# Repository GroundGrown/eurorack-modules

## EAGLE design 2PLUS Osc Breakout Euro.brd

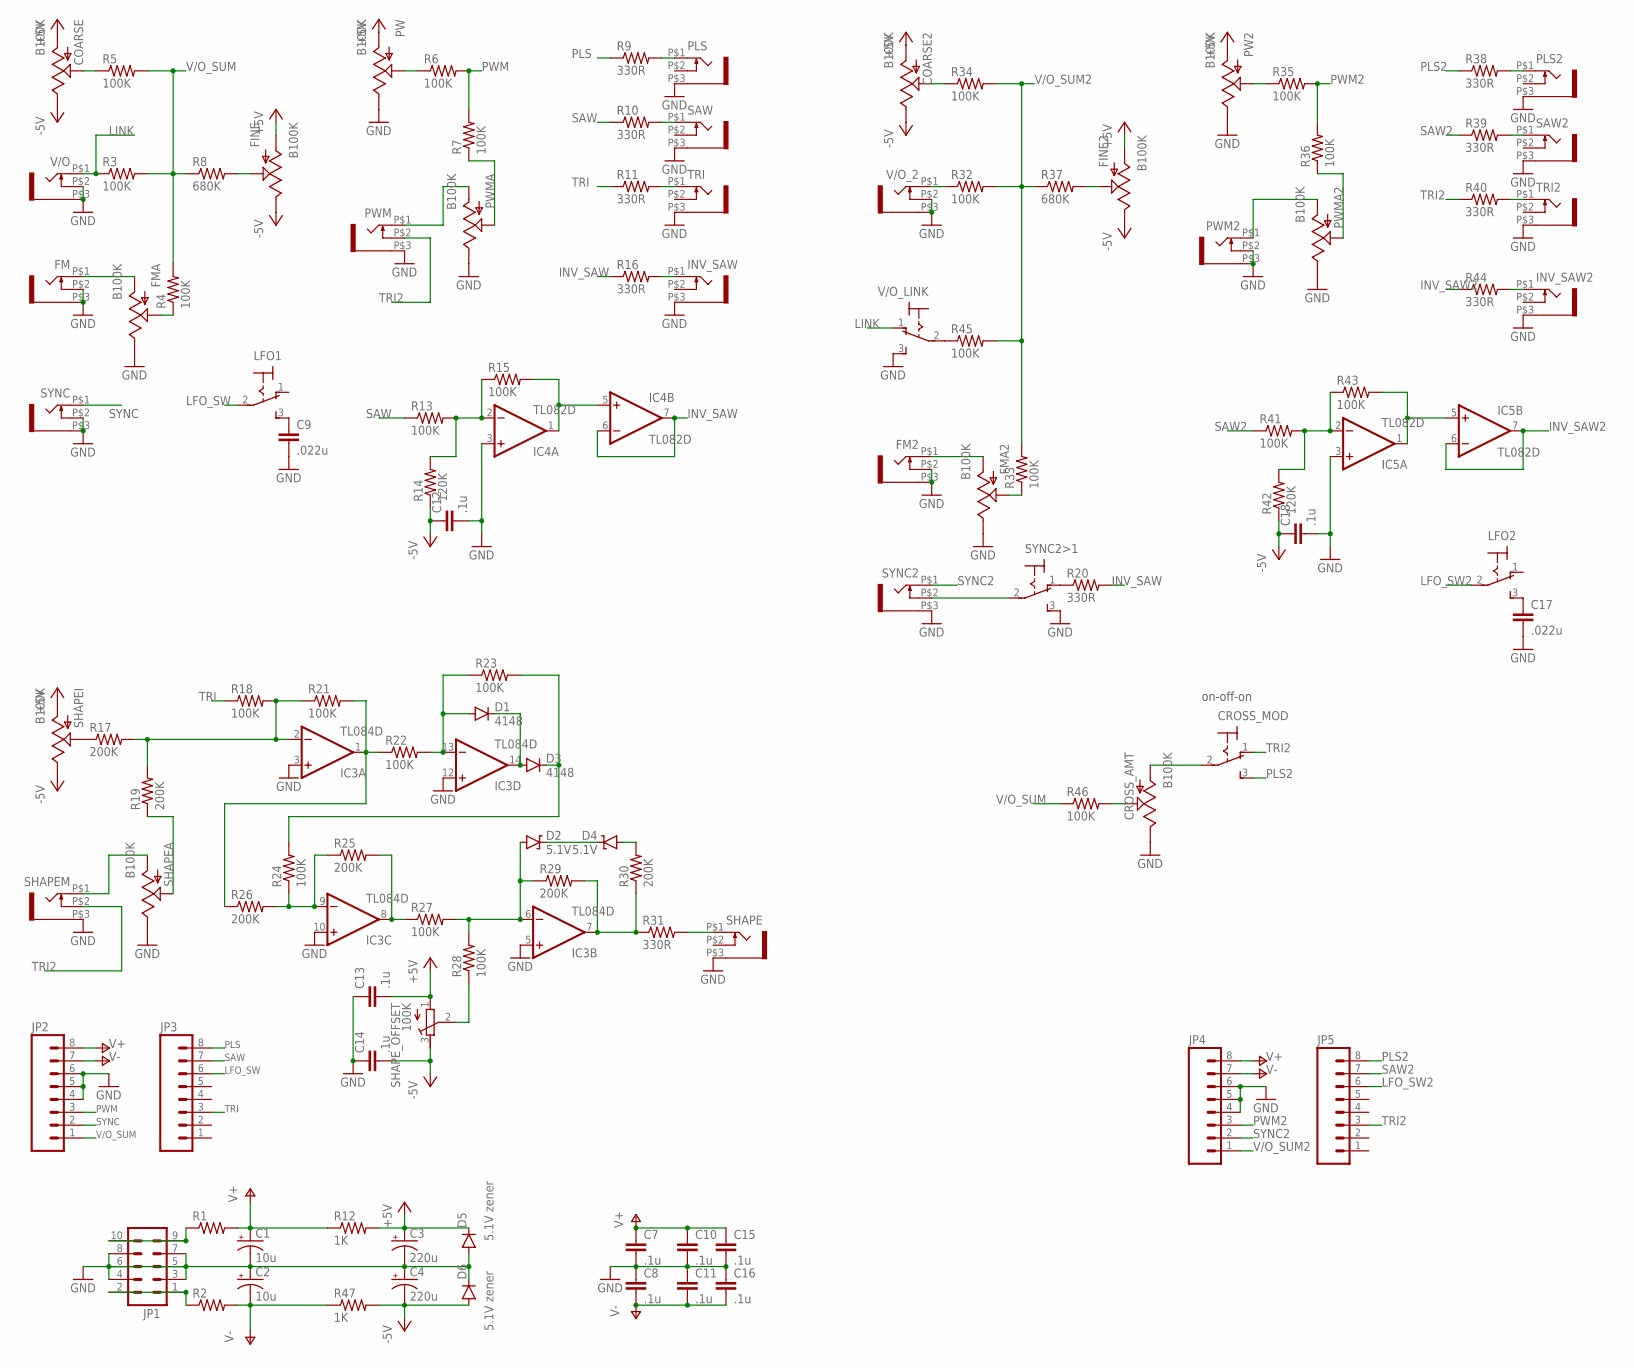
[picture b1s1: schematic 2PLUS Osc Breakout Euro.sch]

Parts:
C1, C2: 10u; PANASONIC_C
C3, C4: 220u; E2,5-5
C7, C8, C10, C11, C12, C13, C14, C15, C16, C18: .1u; 0805
C9, C17: .022u; 0805
COARSE, COARSE2: B100K; ALPS_POT
CROSS_AMT: B100K; ALPS_POT
CROSS_MOD: M9040P
D1, D3: 4148; SOD-123
D2, D4: 5.1V; SOD-123
D5, D6: 5.1V zener; SOD-123
FINE, FINE2: B100K; ALPS_POT
FM, FM2: WQP-PJ301M-12_JACK
FMA, FMA2: B100K; ALPS_POT
IC3: TL084D; SO14
IC4, IC5: TL082D; SO08
INV_SAW, INV_SAW2: WQP-PJ301M-12_JACK
JP1: M05X2PTH; AVR_ICSP
JP2, JP3, JP4, JP5: M08; 1X08_ROUND
LFO1, LFO2: M9040P
PLS, PLS2: WQP-PJ301M-12_JACK
PW, PW2: B100K; ALPS_POT
PWM, PWM2: WQP-PJ301M-12_JACK
PWMA, PWMA2: B100K; ALPS_POT
R1, R2: RESISTOR0805-RES; 0805
R3, R4, R5, R6, R7, R13, R15, R18, R21, R22, R23, R24, R27, R28, R32, R33, R34, R35, R36, R41, R43, R45, R46: 100K; 0805
R8, R37: 680K; 0805
R9, R10, R11, R16, R20, R31, R38, R39, R40, R44: 330R; 0805
R12, R47: 1K; 0805
R14, R42: 120K; 0805
R17, R19, R25, R26, R29, R30: 200K; 0805
SAW, SAW2: WQP-PJ301M-12_JACK
SHAPE: WQP-PJ301M-12_JACK
SHAPEA: B100K; ALPS_POT
SHAPEI: B100K; ALPS_POT
SHAPEM: WQP-PJ301M-12_JACK
SHAPE_OFFSET: 100K; RTRIM3296Y
SYNC, SYNC2: WQP-PJ301M-12_JACK
SYNC2>1: M9040P
TRI, TRI2: WQP-PJ301M-12_JACK
V/O: WQP-PJ301M-12_JACK
V/O_2: WQP-PJ301M-12_JACK
V/O_LINK: M9040P

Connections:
+5V: C3.+, C13.2, COARSE.P$3 (A), COARSE2.P$3 (A), D5.C, FINE.P$3 (A), FINE2.P$3 (A), PW.P$3 (A), PW2.P$3 (A), R12.2, SHAPEI.P$3 (A), SHAPE_OFFSET.1 (A)
-5V: C4.-, C12.1, C14.2, C18.1, COARSE.P$1 (E), COARSE2.P$1 (E), D6.A, FINE.P$1 (E), FINE2.P$1 (E), R14.1, R42.1, R47.2, SHAPEI.P$1 (E), SHAPE_OFFSET.3 (E)
GND: C1.-, C2.+, C3.-, C4.+, C7.2, C8.1, C9.2, C10.2, C11.1, C12.2, C13.1, C14.1, C15.2, C16.1, C17.2, C18.2, CROSS_AMT.P$1 (E), D5.A, D6.C, FM.P$2 (3), FM.P$3 (1), FM2.P$2 (3), FM2.P$3 (1), FMA.P$1 (E), FMA2.P$1 (E), IC3.3 (+IN), IC3.5 (+IN), IC3.10 (+IN), IC3.12 (+IN), IC4.3 (+IN), IC5.3 (+IN), INV_SAW.P$3 (1), INV_SAW2.P$3 (1), JP1.3, JP1.4, JP1.5, JP1.6, JP1.7, JP1.8, JP2.4, JP2.5, JP2.6, JP4.4, JP4.5, JP4.6, PLS.P$3 (1), PLS2.P$3 (1), PW.P$1 (E), PW2.P$1 (E), PWM.P$3 (1), PWM2.P$2 (3), PWM2.P$3 (1), PWMA.P$1 (E), PWMA2.P$1 (E), SAW.P$3 (1), SAW2.P$3 (1), SHAPE.P$3 (1), SHAPEA.P$1 (E), SHAPEM.P$3 (1), SYNC.P$2 (3), SYNC.P$3 (1), SYNC2.P$3 (1), SYNC2>1.3 (S), TRI.P$3 (1), TRI2.P$3 (1), V/O.P$2 (3), V/O.P$3 (1), V/O_2.P$2 (3), V/O_2.P$3 (1), V/O_LINK.3 (S)
INV_SAW: IC4.6 (-IN), IC4.7 (OUT), R16.1, R20.2
INV_SAW2: IC5.6 (-IN), IC5.7 (OUT), R44.1
LFO_SW: JP3.6, LFO1.2
LFO_SW2: JP5.6, LFO2.2
LINK: R3.1, V/O.P$1 (2), V/O_LINK.1 (O)
unnamed: JP1.9, JP1.10, R1.1
unnamed: JP1.1, JP1.2, R2.1
unnamed: FM.P$1 (2), FMA.P$3 (A)
unnamed: COARSE.P$2 (S), R5.1
unnamed: R45.1, V/O_LINK.2
unnamed: FMA.P$2 (S), R4.1
unnamed: PW.P$2 (S), R6.1
unnamed: PWM.P$1 (2), PWMA.P$3 (A)
unnamed: FINE.P$2 (S), R8.2
unnamed: C9.1, LFO1.3 (S)
unnamed: PWMA.P$2 (S), R7.1
unnamed: PLS.P$1 (2), R9.2
unnamed: R10.2, SAW.P$1 (2)
unnamed: R11.2, TRI.P$1 (2)
unnamed: IC4.2 (-IN), R13.2, R14.2, R15.1
unnamed: IC3.2 (-IN), R17.2, R18.2, R19.2, R21.1
unnamed: IC4.1 (OUT), IC4.5 (+IN), R15.2
unnamed: CROSS_AMT.P$2 (S), R46.2
unnamed: INV_SAW.P$1 (2), R16.2
unnamed: R17.1, SHAPEI.P$2 (S)
unnamed: SHAPEA.P$3 (A), SHAPEM.P$1 (2)
unnamed: R19.1, SHAPEA.P$2 (S)
unnamed: SYNC2.P$2 (3), SYNC2>1.2
unnamed: IC3.1 (OUT), R21.2, R22.1, R26.1
unnamed: D1.C, D3.A, IC3.14 (OUT)
unnamed: D1.A, IC3.13 (-IN), R22.2, R23.1
unnamed: D3.C, R23.2, R24.2
unnamed: IC3.9 (-IN), R24.1, R25.1, R26.2
unnamed: IC3.8 (OUT), R25.2, R27.1
unnamed: D2.A, IC3.6 (-IN), R27.2, R28.2, R29.1
unnamed: R28.1, SHAPE_OFFSET.2 (S)
unnamed: D2.C, D4.C
unnamed: D4.A, R30.2
unnamed: IC3.7 (OUT), R29.2, R30.1, R31.1
unnamed: R31.2, SHAPE.P$1 (2)
unnamed: COARSE2.P$2 (S), R34.1
unnamed: R32.1, V/O_2.P$1 (2)
unnamed: CROSS_AMT.P$3 (A), CROSS_MOD.2
unnamed: FMA2.P$2 (S), R33.1
unnamed: C17.1, LFO2.3 (S)
unnamed: PW2.P$2 (S), R35.1
unnamed: FINE2.P$2 (S), R37.2
unnamed: PLS2.P$1 (2), R38.2
unnamed: R39.2, SAW2.P$1 (2)
unnamed: R40.2, TRI2.P$1 (2)
unnamed: FM2.P$1 (2), FMA2.P$3 (A)
unnamed: PWM2.P$1 (2), PWMA2.P$3 (A)
unnamed: INV_SAW2.P$1 (2), R44.2
unnamed: PWMA2.P$2 (S), R36.1
unnamed: R20.1, SYNC2>1.1 (O)
unnamed: IC5.2 (-IN), R41.2, R42.2, R43.1
unnamed: IC5.1 (OUT), IC5.5 (+IN), R43.2
PLS: JP3.8, R9.1
PLS2: CROSS_MOD.3 (S), JP5.8, R38.1
PWM: JP2.3, R6.2, R7.2
PWM2: JP4.3, R35.2, R36.2
SAW: JP3.7, R10.1, R13.1
SAW2: JP5.7, R39.1, R41.1
SYNC: JP2.2, SYNC.P$1 (2)
SYNC2: JP4.2, SYNC2.P$1 (2)
TRI: JP3.3, R11.1, R18.1
TRI2: CROSS_MOD.1 (O), JP5.3, PWM.P$2 (3), R40.1, SHAPEM.P$2 (3)
V+: C1.+, C7.1, C10.1, C15.1, IC3.4 (V+), IC4.8 (V+), IC5.8 (V+), JP2.8, JP4.8, R1.2, R12.1
V-: C2.-, C8.2, C11.2, C16.2, IC3.11 (V-), IC4.4 (V-), IC5.4 (V-), JP2.7, JP4.7, R2.2, R47.1
V/O_SUM: JP2.1, R3.2, R4.2, R5.2, R8.1, R46.1
V/O_SUM2: JP4.1, R32.2, R33.2, R34.2, R37.1, R45.2

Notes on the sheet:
on-off-on

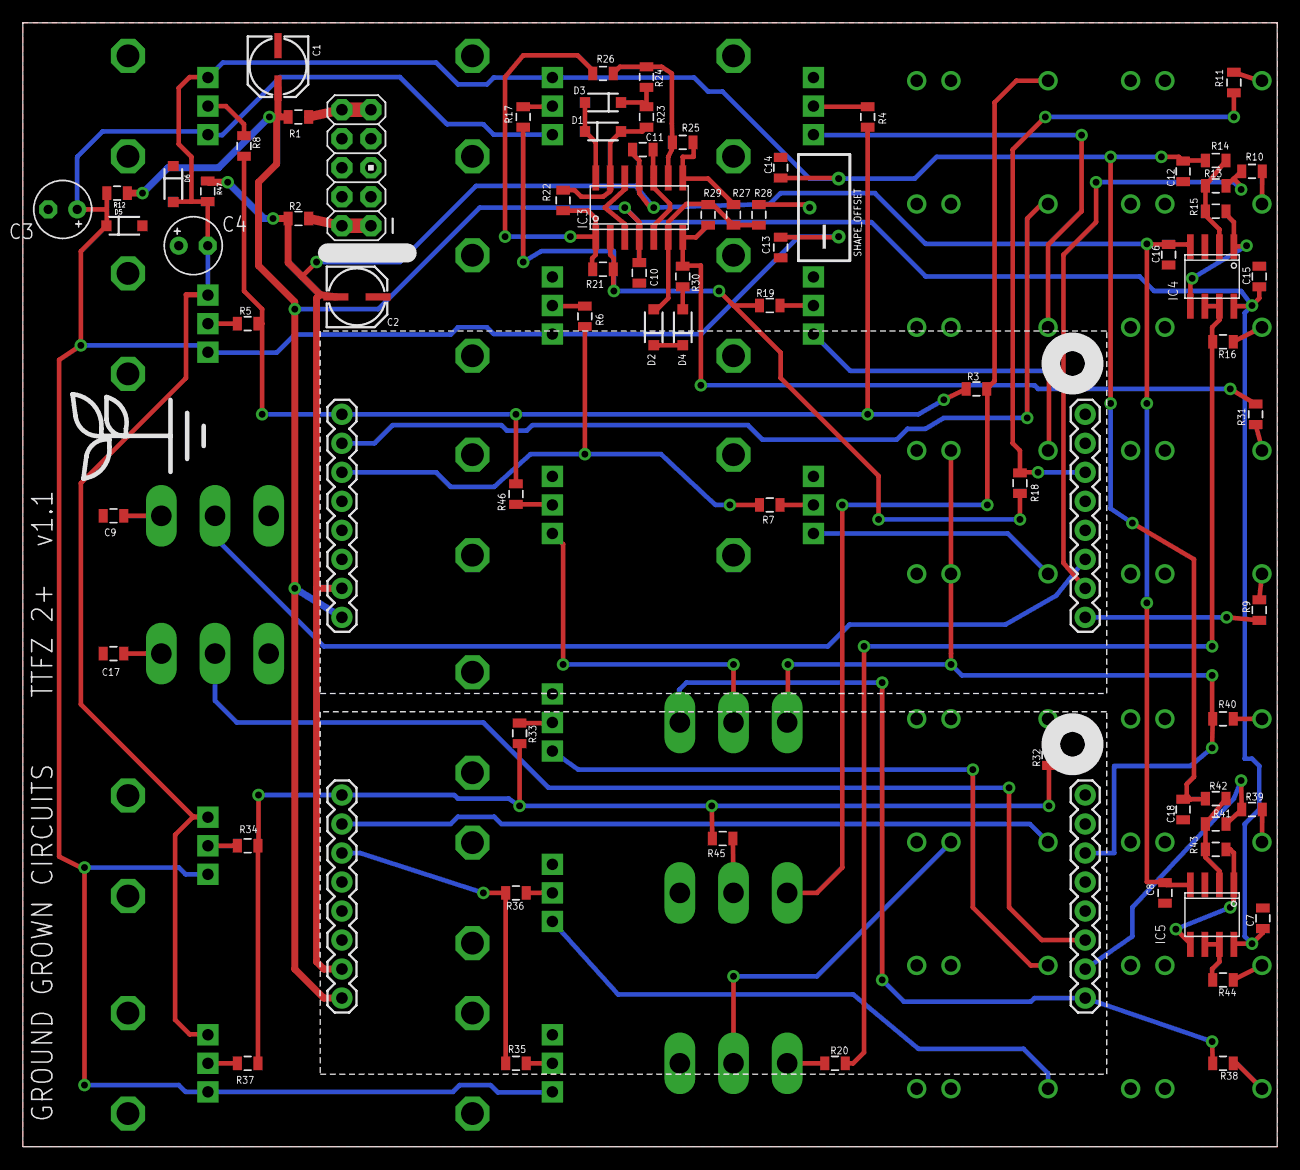
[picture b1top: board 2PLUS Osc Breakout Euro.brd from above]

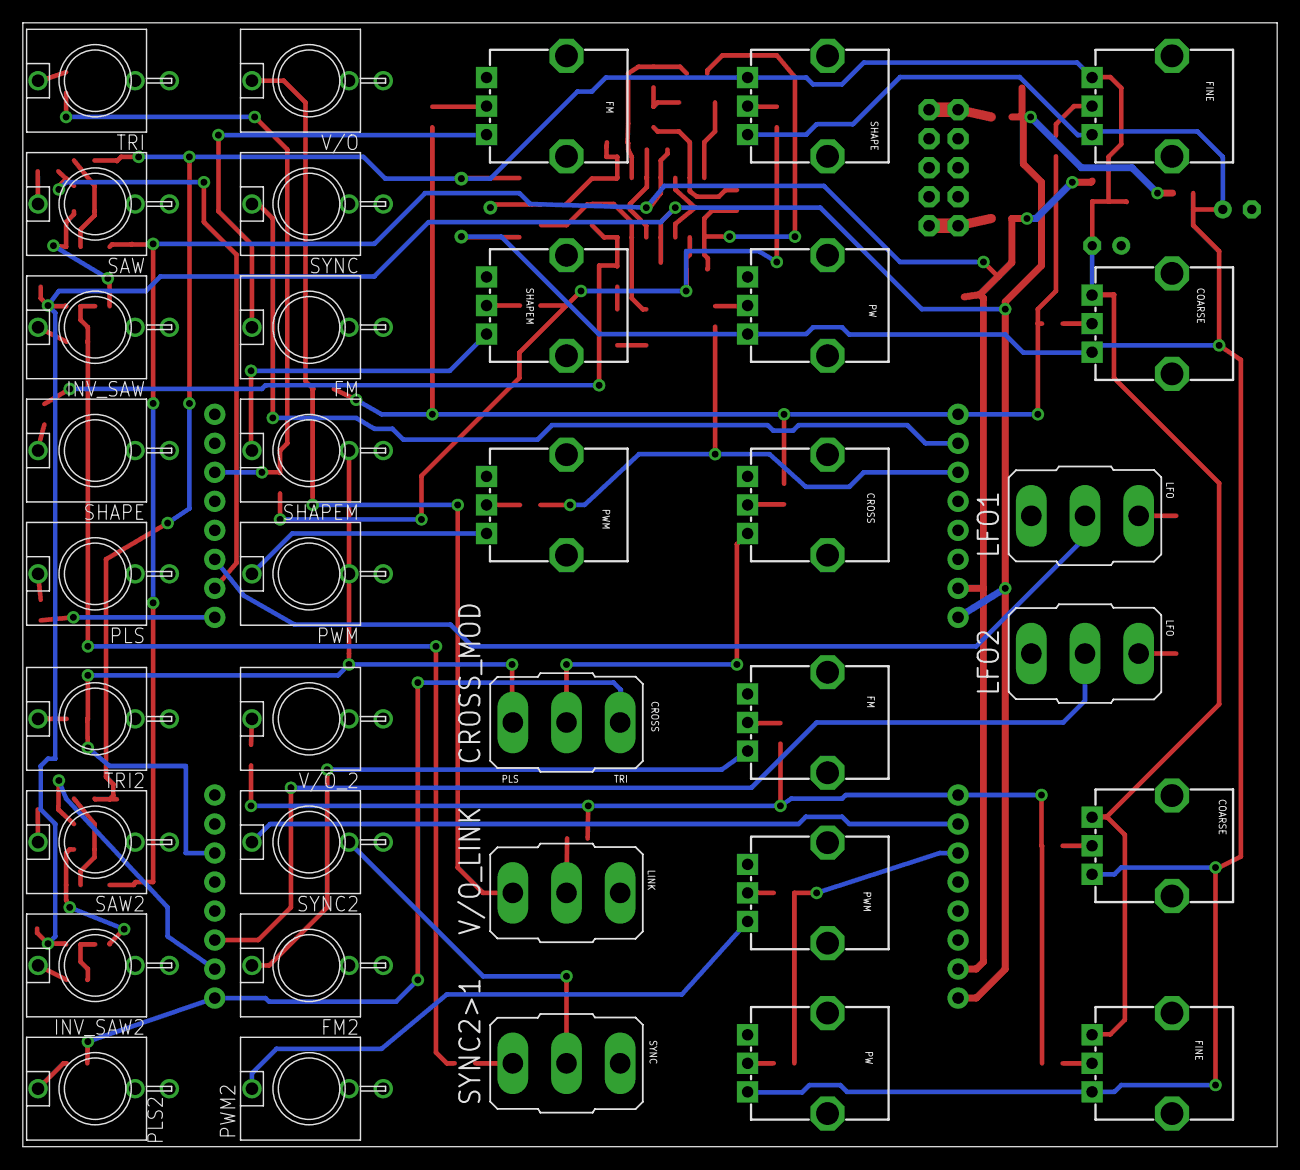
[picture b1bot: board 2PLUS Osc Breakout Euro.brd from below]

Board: 2 copper layers, 109.8 x 98.4 mm, 117 parts (36 on the bottom side), 74 nets.

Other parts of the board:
U$1, U$2: OSC_CORE_OUTLINE
U$3: LOGO_MED

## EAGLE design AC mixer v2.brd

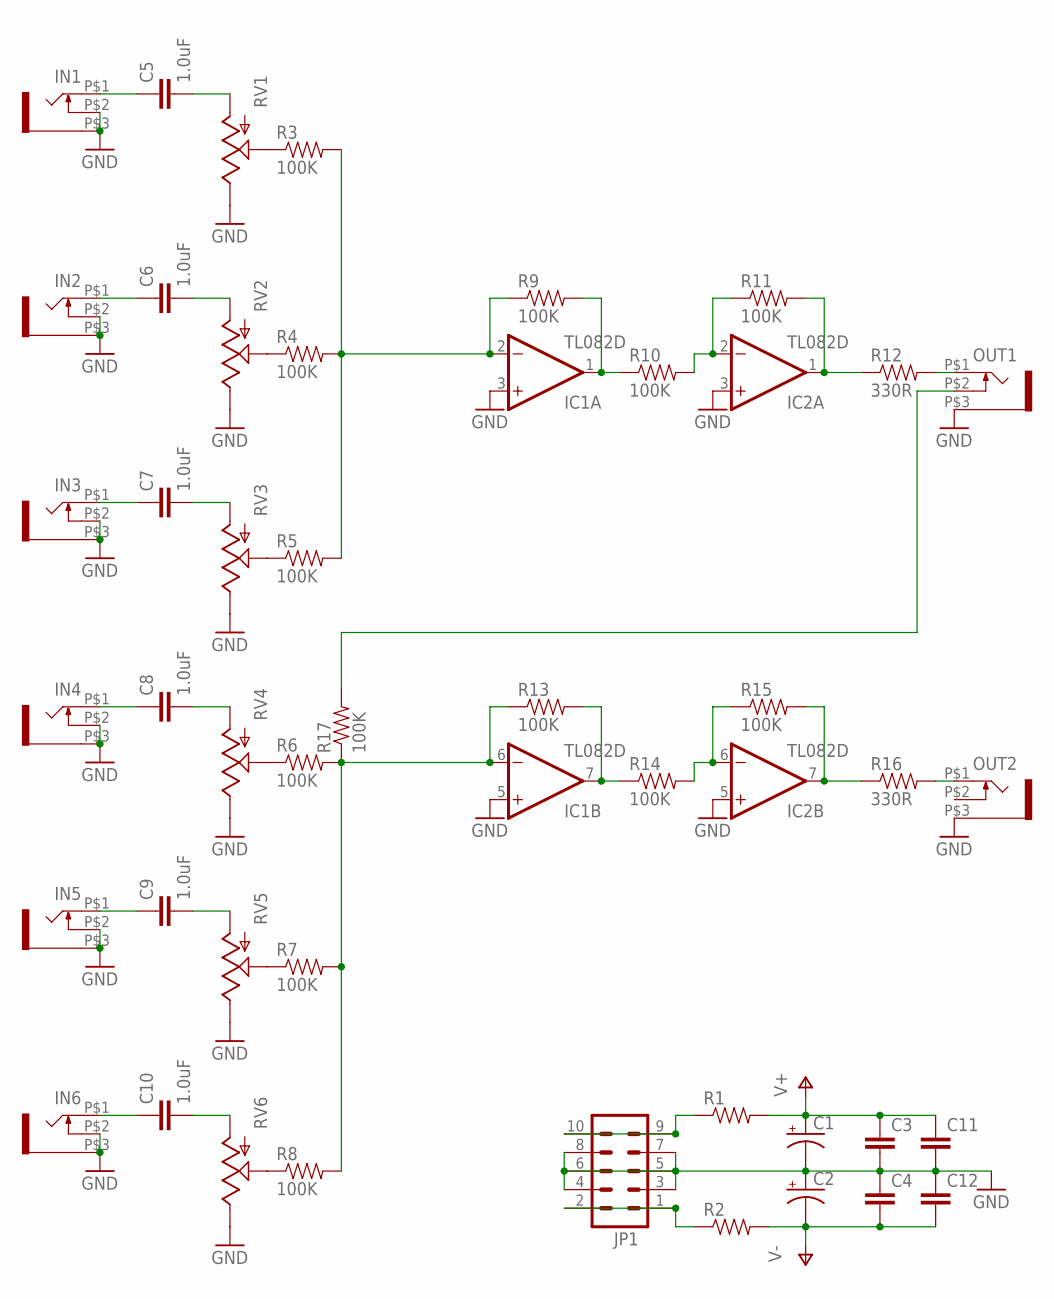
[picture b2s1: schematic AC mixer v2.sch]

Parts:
C1, C2: CAP_POLC; PANASONIC_C
C3, C4, C11, C12: CAP0805; 0805
C5, C6, C7, C8, C9, C10: 1.0uF; 1206
IC1, IC2: TL082D; SO08
IN1, IN2, IN3, IN4, IN5, IN6: WQP-PJ301M-12_JACK
JP1: M05X2PTH; AVR_ICSP
OUT1, OUT2: WQP-PJ301M-12_JACK
R1, R2: RESISTOR0805-RES; 0805
R3, R4, R5, R6, R7, R8, R9, R10, R11, R13, R14, R15, R17: 100K; 0805
R12, R16: 330R; 0805
RV1, RV2, RV3, RV4, RV5, RV6: POT; ALPS_POT

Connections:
GND: C1.-, C2.+, C3.2, C4.1, C11.2, C12.1, IC1.3 (+IN), IC1.5 (+IN), IC2.3 (+IN), IC2.5 (+IN), IN1.P$2 (3), IN1.P$3 (1), IN2.P$2 (3), IN2.P$3 (1), IN3.P$2 (3), IN3.P$3 (1), IN4.P$2 (3), IN4.P$3 (1), IN5.P$2 (3), IN5.P$3 (1), IN6.P$2 (3), IN6.P$3 (1), JP1.3, JP1.4, JP1.5, JP1.6, JP1.7, JP1.8, OUT1.P$3 (1), OUT2.P$3 (1), RV1.P$1 (E), RV2.P$1 (E), RV3.P$1 (E), RV4.P$1 (E), RV5.P$1 (E), RV6.P$1 (E)
unnamed: R3.1, RV1.P$2 (S)
unnamed: C6.1, IN2.P$1 (2)
unnamed: JP1.9, JP1.10, R1.1
unnamed: C6.2, RV2.P$3 (A)
unnamed: R4.1, RV2.P$2 (S)
unnamed: JP1.1, JP1.2, R2.1
unnamed: C7.1, IN3.P$1 (2)
unnamed: C7.2, RV3.P$3 (A)
unnamed: C5.1, IN1.P$1 (2)
unnamed: C5.2, RV1.P$3 (A)
unnamed: R5.1, RV3.P$2 (S)
unnamed: C8.1, IN4.P$1 (2)
unnamed: C8.2, RV4.P$3 (A)
unnamed: R6.1, RV4.P$2 (S)
unnamed: C9.1, IN5.P$1 (2)
unnamed: C9.2, RV5.P$3 (A)
unnamed: R7.1, RV5.P$2 (S)
unnamed: C10.1, IN6.P$1 (2)
unnamed: C10.2, RV6.P$3 (A)
unnamed: R8.1, RV6.P$2 (S)
unnamed: OUT1.P$2 (3), R17.2
unnamed: IC1.1 (OUT), R9.2, R10.1
unnamed: IC2.2 (-IN), R10.2, R11.1
unnamed: IC2.1 (OUT), R11.2, R12.1
unnamed: OUT1.P$1 (2), R12.2
unnamed: IC1.2 (-IN), R3.2, R4.2, R5.2, R9.1
unnamed: IC1.7 (OUT), R13.2, R14.1
unnamed: IC2.6 (-IN), R14.2, R15.1
unnamed: IC2.7 (OUT), R15.2, R16.1
unnamed: OUT2.P$1 (2), R16.2
unnamed: IC1.6 (-IN), R6.2, R7.2, R8.2, R13.1, R17.1
V+: C1.+, C3.1, C11.1, IC1.8 (V+), IC2.8 (V+), R1.2
V-: C2.-, C4.2, C12.2, IC1.4 (V-), IC2.4 (V-), R2.2

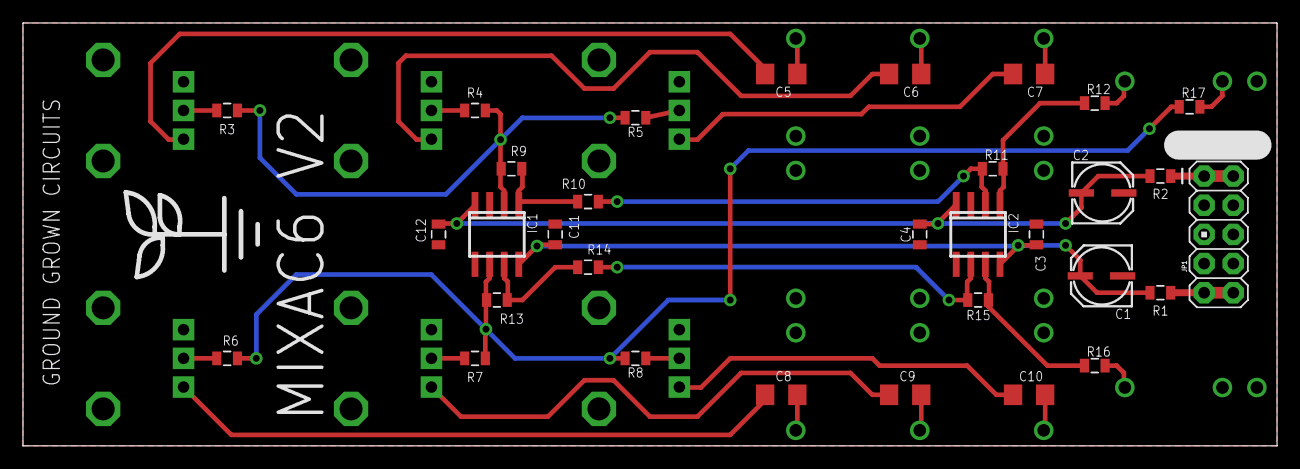
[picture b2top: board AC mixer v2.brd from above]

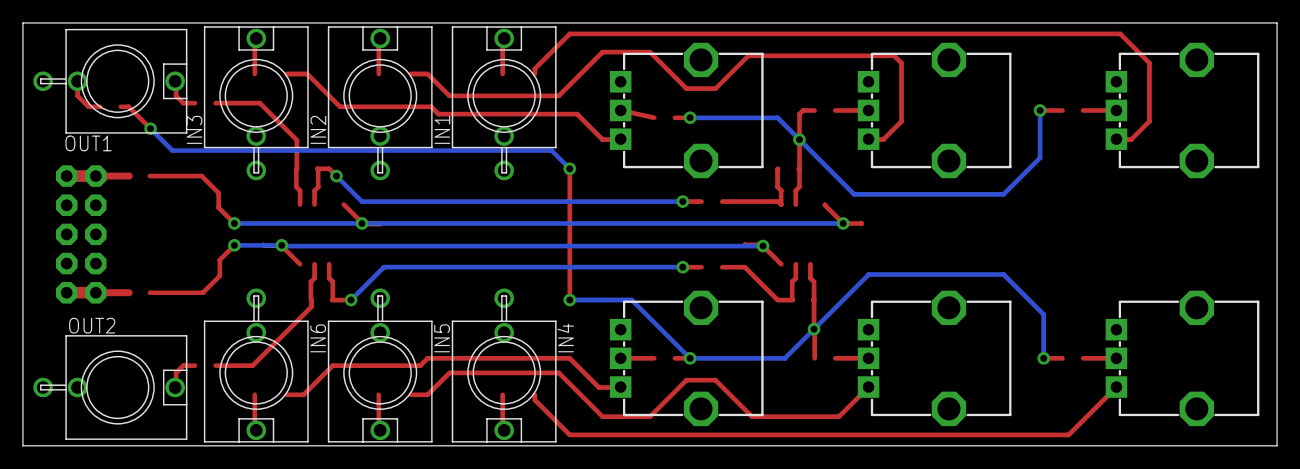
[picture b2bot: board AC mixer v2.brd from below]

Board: 2 copper layers, 109.2 x 36.8 mm, 47 parts (14 on the bottom side), 34 nets.

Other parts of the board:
U$1: LOGO_MED

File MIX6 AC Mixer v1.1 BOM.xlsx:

2 | FERRITE BEAD | R1, R2
1 | 330 ohm | R12
9 | 100K | R3, R4, R5, R6, R7, R8, R9, R10, R11
2 | .1u | C3, C4
6 | 1u Film | C5, C6, C7, C8, C9, C10
2 | 10u | C1, C2
1 | TL082 | IC1
1 | 2x5 pos male .1" Header | JP1
7 | WQP-PJ301M-12_JACK | IN1, IN2, IN3, IN4, IN5, IN6, OUT
6 | B50K | RV1, RV2, RV3, RV4, RV5, RV6

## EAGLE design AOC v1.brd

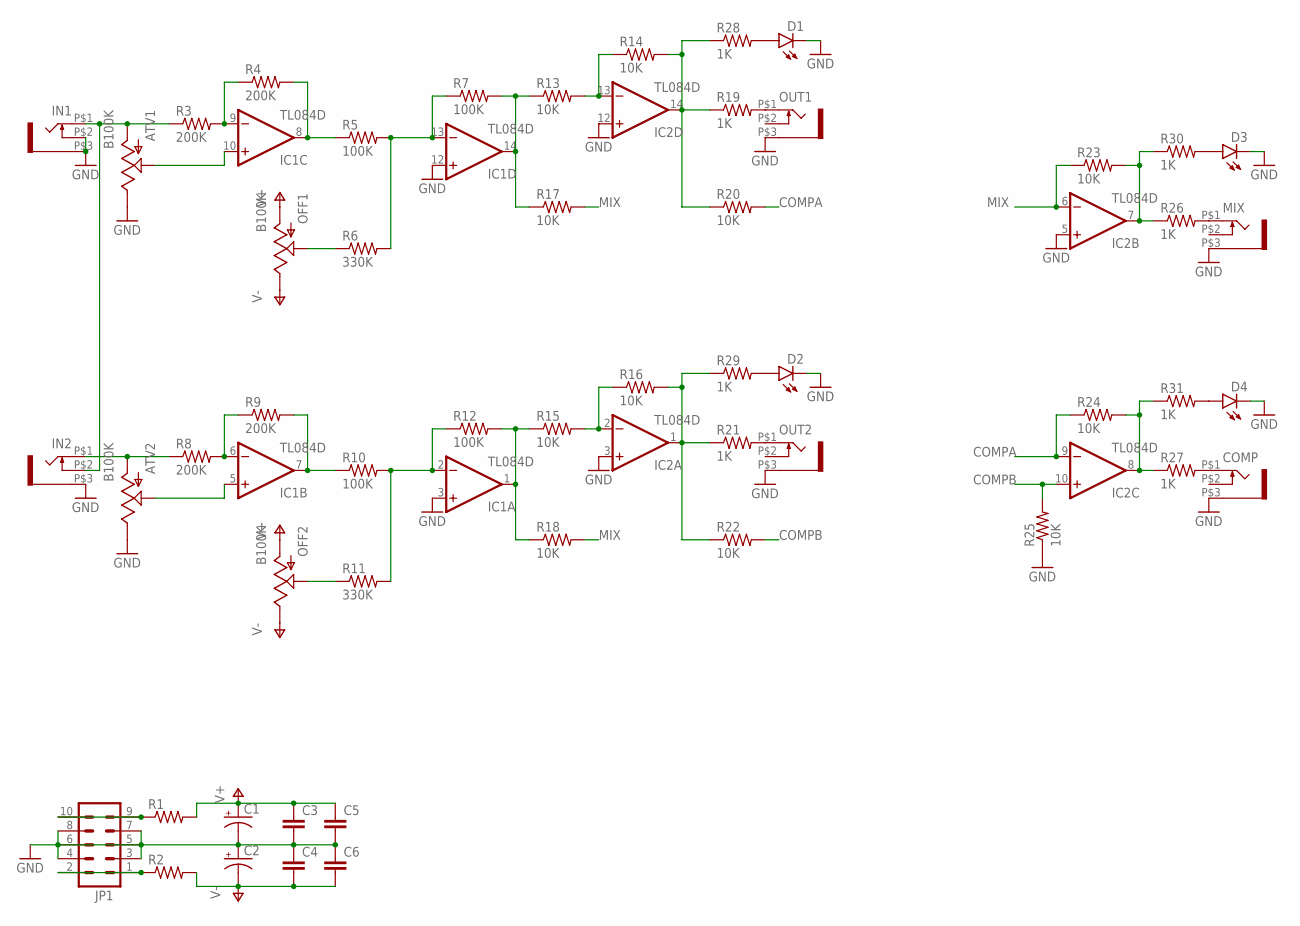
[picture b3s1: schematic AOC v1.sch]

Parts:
ATV1, ATV2: B100K; ALPS_POT
C1, C2: CAP_POLPTH2; CPOL-RADIAL-10UF-25V
C3, C4, C5, C6: CAP0805; 0805
COMP: WQP-PJ301M-12_JACK
D1, D2, D3, D4: LED3MM
IC1, IC2: TL084D; SO14
IN1, IN2: WQP-PJ301M-12_JACK
JP1: M05X2PTH; AVR_ICSP
MIX: WQP-PJ301M-12_JACK
OFF1, OFF2: B100K; ALPS_POT
OUT1, OUT2: WQP-PJ301M-12_JACK
R1, R2: RESISTOR0805-RES; 0805@1
R3, R4, R8, R9: 200K; 0805@1
R5, R7, R10, R12: 100K; 0805@1
R6, R11: 330K; 0805@1
R13, R14, R15, R16, R17, R18, R20, R22, R23, R24, R25: 10K; 0805@1
R19, R21, R26, R27, R28, R29, R30, R31: 1K; 0805@1

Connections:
COMPA: IC2.9 (-IN), R20.2, R24.1
COMPB: IC2.10 (+IN), R22.2, R25.2
GND: ATV1.P$1 (E), ATV2.P$1 (E), C1.2 (-), C2.1 (+), C3.2, C4.1, C5.2, C6.1, COMP.P$3 (1), D1.K (C), D2.K (C), D3.K (C), D4.K (C), IC1.3 (+IN), IC1.12 (+IN), IC2.3 (+IN), IC2.5 (+IN), IC2.12 (+IN), IN1.P$2 (3), IN1.P$3 (1), IN2.P$3 (1), JP1.3, JP1.4, JP1.5, JP1.6, JP1.7, JP1.8, MIX.P$3 (1), OUT1.P$3 (1), OUT2.P$3 (1), R25.1
MIX: IC2.6 (-IN), R17.2, R18.2, R23.1
unnamed: JP1.9, JP1.10, R1.1
unnamed: JP1.1, JP1.2, R2.1
unnamed: IC1.9 (-IN), R3.2, R4.1
unnamed: ATV1.P$3 (A), IN1.P$1 (2), IN2.P$2 (3), R3.1
unnamed: IC1.8 (OUT), R4.2, R5.1
unnamed: ATV1.P$2 (S), IC1.10 (+IN)
unnamed: OFF1.P$2 (S), R6.1
unnamed: IC1.13 (-IN), R5.2, R6.2, R7.1
unnamed: IC1.14 (OUT), R7.2, R13.1, R17.1
unnamed: IC1.6 (-IN), R8.2, R9.1
unnamed: ATV2.P$3 (A), IN2.P$1 (2), R8.1
unnamed: IC1.7 (OUT), R9.2, R10.1
unnamed: ATV2.P$2 (S), IC1.5 (+IN)
unnamed: OFF2.P$2 (S), R11.1
unnamed: IC1.2 (-IN), R10.2, R11.2, R12.1
unnamed: IC1.1 (OUT), R12.2, R15.1, R18.1
unnamed: IC2.13 (-IN), R13.2, R14.1
unnamed: IC2.14 (OUT), R14.2, R19.1, R20.1, R28.1
unnamed: IC2.2 (-IN), R15.2, R16.1
unnamed: IC2.1 (OUT), R16.2, R21.1, R22.1, R29.1
unnamed: MIX.P$1 (2), R26.2
unnamed: IC2.7 (OUT), R23.2, R26.1, R30.1
unnamed: OUT1.P$1 (2), R19.2
unnamed: OUT2.P$1 (2), R21.2
unnamed: IC2.8 (OUT), R24.2, R27.1, R31.1
unnamed: COMP.P$1 (2), R27.2
unnamed: D1.A, R28.2
unnamed: D2.A, R29.2
unnamed: D3.A, R30.2
unnamed: D4.A, R31.2
V+: C1.1 (+), C3.1, C5.1, IC1.4 (V+), IC2.4 (V+), OFF1.P$3 (A), OFF2.P$3 (A), R1.2
V-: C2.2 (-), C4.2, C6.2, IC1.11 (V-), IC2.11 (V-), OFF1.P$1 (E), OFF2.P$1 (E), R2.2

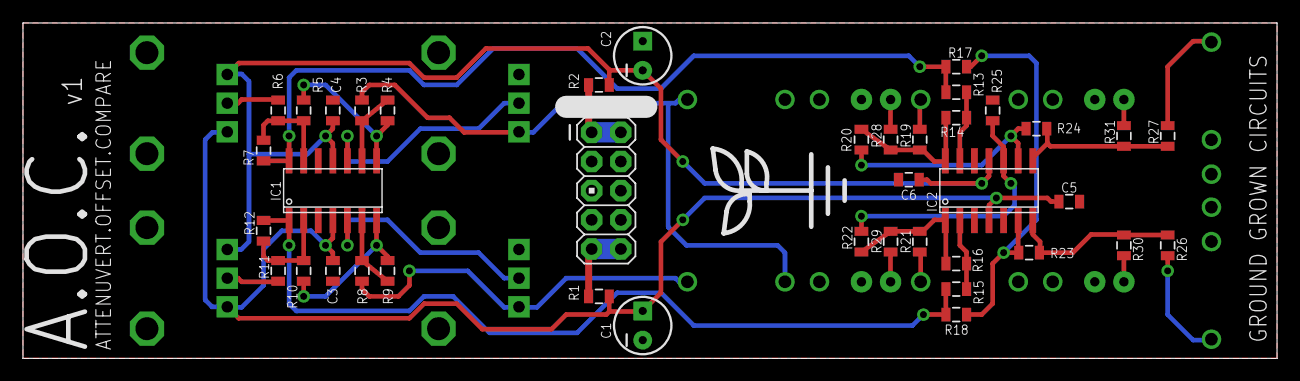
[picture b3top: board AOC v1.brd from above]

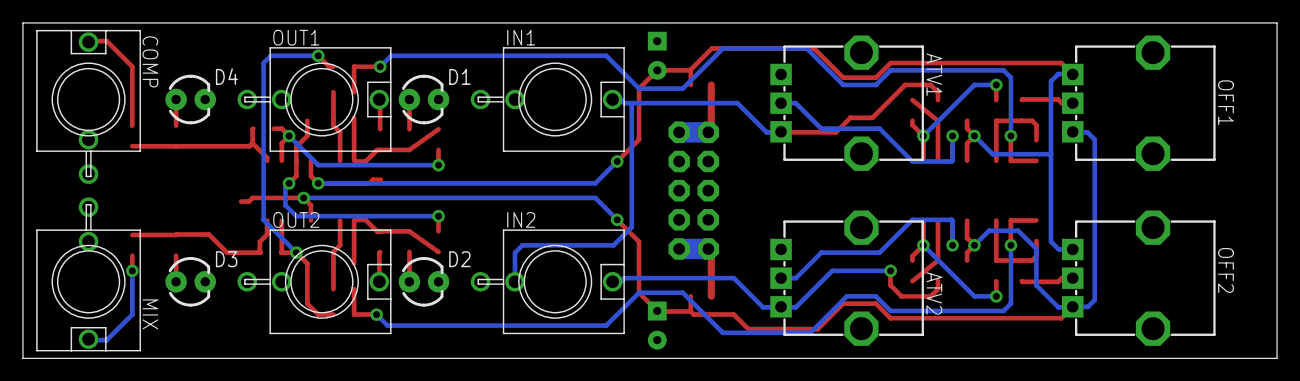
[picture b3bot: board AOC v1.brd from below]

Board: 2 copper layers, 109.2 x 29.2 mm, 55 parts (14 on the bottom side), 36 nets.

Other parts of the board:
U$1: LOGO_MED

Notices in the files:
parts and their libraries:
SparkFun-Capacitors: Licensing: Creative Commons ShareAlike 4.0 International - https://creativecommons.org/licenses/by-sa/4.0
